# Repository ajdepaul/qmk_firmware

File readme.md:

# Custom 14x5 Keyboard QMK Fork

Forked from: https://github.com/qmk/qmk_firmware

I followed [this](https://github.com/ruiqimao/keyboard-pcb-guide) guide to design the PCB.

- KiCad PCB files can be found in the [pcb](pcb) directory.
- KiCad PCB files for a switch plate can found in the [plate](plate) directory.
- Laser cut case files can be found in the [case](case) directory.

Build with QMK CLI: `qmk compile -kb kb -km default`

Notes:
- I did not originally design the PCB with holes for screws. I ended up drilling
  holes in the PCB in safe locations for screws. The screw holes in the acrylic
  case cutouts line up with the holes that I drilled personally. If you want to
  rebuild the board, I recommend adding holes to the PCB and changing the hole
  placements in the acrylic case cutouts to match.
- I did not originally design the PCB with RGB LED strips in mind. The LED strip
  I am using is soldered directly onto some pins of the MCU. If you want RGB LED
  strip support, I recommend adding some soldering points to the PCB.
- I did not fill the PCB for the switch plate with copper, so it flexes a good
  amount. If you want to rebuild the board, I recommend modifying the PCB plate
  and filling it with copper to give a sturdier feel.

## Personal Keyboard Specs

- Switches: Lubed Cherry MX Clear with 62g springs
- Keycaps:
  - [KPrepublic Japanese Root base](https://kprepublic.com/collections/pbt-dye-sub-keycaps/products/kprepublic-139-japanese-root-japan-black-font-language-cherry-profile-dye-sub-keycap-pbt-for-gh60-xd60-xd84-cospad-tada68-87-104)
  - [Muted Copper Koi Fish artisan](https://www.etsy.com/shop/DreamKaps?ref=from_order_confirm_drawer_receipt_modal)
  - Cheap PBT black & gray blanks for modifiers

## Pictures

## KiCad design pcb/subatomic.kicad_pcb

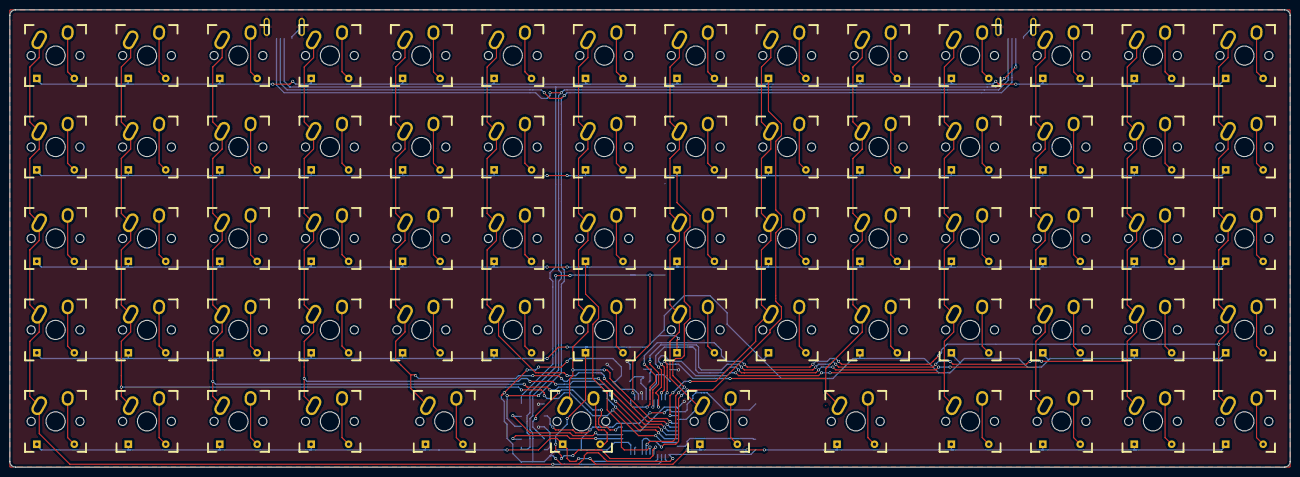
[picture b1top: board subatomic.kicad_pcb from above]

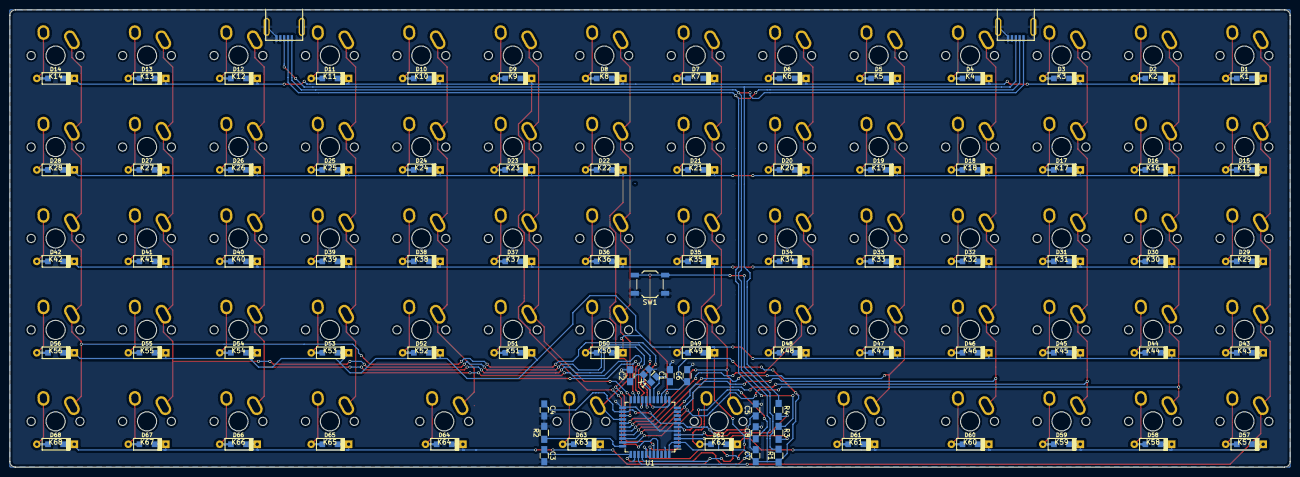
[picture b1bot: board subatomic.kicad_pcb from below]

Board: 2 copper layers, 266.7 x 95.3 mm, 153 parts (85 on the bottom side), 98 nets.

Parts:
C1, C2: 22p; C_0805_HandSoldering
C3, C4, C5, C6: 0.1u; C_0805_HandSoldering
C7: 4.7u; C_0805_HandSoldering
C8: 1u; C_0805_HandSoldering
D1, D2, D3, D4, D5, D6, D7, D8, D9, D10, D11, D12, D13, D14, D15, D16, D17, D18, D19, D20, D21, D22, D23, D24, D25, D26, D27, D28, D29, D30, D31, D32, D33, D34, D35, D36, D37, D38, D39, D40, D41, D42, D43, D44, D45, D46, D47, D48, D49, D50, D51, D52, D53, D54, D55, D56, D57, D58, D59, D60, D61, D62, D63, D64, D65, D66, D67, D68: D; D_SOD123_axial
J1, J2: USB_mini_micro_B; USB_miniB_hirose_5S8
K1, K2, K3, K4, K5, K6, K7, K8, K9, K10, K11, K12, K13, K14, K15, K16, K17, K18, K19, K20, K21, K22, K23, K24, K25, K26, K27, K28, K29, K30, K31, K32, K33, K34, K35, K36, K37, K38, K39, K40, K41, K42, K43, K44, K45, K46, K47, K48, K49, K50, K51, K52, K53, K54, K55, K56, K57, K58, K59, K60, K65, K66, K67, K68: KEYSW; Mx_Alps_100
K61, K62, K63, K64: KEYSW; Mx_Alps_150
R1, R2: 10k; R_0805_HandSoldering
R3, R4: 22; R_0805_HandSoldering
SW1: SW_PUSH; SW_SPST_TL3342
U1: ATMEGA32U4; TQFP-44_10x10mm_Pitch0.8mm
X1: XTAL_GND; crystal_FA238-TSX3225

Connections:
/col0: K1.1, K15.1, K29.1, K43.1, K57.1, U1.36
/col1: K2.1, K16.1, K30.1, K44.1, K58.1, U1.32
/col2: K3.1, K17.1, K31.1, K45.1, K59.1, U1.31
/col3: K4.1, K18.1, K32.1, K46.1, K60.1, U1.30
/col4: K5.1, K19.1, K33.1, K47.1, K61.1, U1.29
/col5: K6.1, K20.1, K34.1, K48.1, U1.28
/col6: K7.1, K21.1, K35.1, K49.1, K62.1, U1.27
/col7: K8.1, K22.1, K36.1, K50.1, K63.1, U1.26
/col8: K9.1, K23.1, K37.1, K51.1, U1.25
/col9: K10.1, K24.1, K38.1, K52.1, K64.1, U1.21
/col10: K11.1, K25.1, K39.1, K53.1, K65.1, U1.20
/col11: K12.1, K26.1, K40.1, K54.1, K66.1, U1.19
/col12: K13.1, K27.1, K41.1, K55.1, K67.1, U1.18
/col13: K14.1, K28.1, K42.1, K56.1, K68.1, U1.12
/row0: D1.1, D2.1, D3.1, D4.1, D5.1, D6.1, D7.1, D8.1, D9.1, D10.1, D11.1, D12.1, D13.1, D14.1, U1.41
/row1: D15.1, D16.1, D17.1, D18.1, D19.1, D20.1, D21.1, D22.1, D23.1, D24.1, D25.1, D26.1, D27.1, D28.1, U1.40
/row2: D29.1, D30.1, D31.1, D32.1, D33.1, D34.1, D35.1, D36.1, D37.1, D38.1, D39.1, D40.1, D41.1, D42.1, U1.39
/row3: D43.1, D44.1, D45.1, D46.1, D47.1, D48.1, D49.1, D50.1, D51.1, D52.1, D53.1, D54.1, D55.1, D56.1, U1.38
/row4: D57.1, D58.1, D59.1, D60.1, D61.1, D62.1, D63.1, D64.1, D65.1, D66.1, D67.1, D68.1, U1.37
GND: C1.2, C2.2, C3.2, C4.2, C5.2, C6.2, C7.2, C8.2, J1.5, J1.6, J2.5, J2.6, R2.2, SW1.1, U1.5, U1.15, U1.23, U1.35, U1.43, X1.3
unnamed: C1.1, U1.16, X1.1
unnamed: C2.1, U1.17, X1.2
unnamed: C8.1, U1.6
unnamed: D1.2, K1.2
unnamed: D2.2, K2.2
unnamed: D3.2, K3.2
unnamed: D4.2, K4.2
unnamed: D5.2, K5.2
unnamed: D6.2, K6.2
unnamed: D7.2, K7.2
unnamed: D8.2, K8.2
unnamed: D9.2, K9.2
unnamed: D10.2, K10.2
unnamed: D11.2, K11.2
unnamed: D12.2, K12.2
unnamed: D13.2, K13.2
unnamed: D14.2, K14.2
unnamed: D15.2, K15.2
unnamed: D16.2, K16.2
unnamed: D17.2, K17.2
unnamed: D18.2, K18.2
unnamed: D19.2, K19.2
unnamed: D20.2, K20.2
unnamed: D21.2, K21.2
unnamed: D22.2, K22.2
unnamed: D23.2, K23.2
unnamed: D24.2, K24.2
unnamed: D25.2, K25.2
unnamed: D26.2, K26.2
unnamed: D27.2, K27.2
unnamed: D28.2, K28.2
unnamed: D29.2, K29.2
unnamed: D30.2, K30.2
unnamed: D31.2, K31.2
unnamed: D32.2, K32.2
unnamed: D33.2, K33.2
unnamed: D34.2, K34.2
unnamed: D35.2, K35.2
unnamed: D36.2, K36.2
unnamed: D37.2, K37.2
unnamed: D38.2, K38.2
unnamed: D39.2, K39.2
unnamed: D40.2, K40.2
unnamed: D41.2, K41.2
unnamed: D42.2, K42.2
unnamed: D43.2, K43.2
unnamed: D44.2, K44.2
unnamed: D45.2, K45.2
unnamed: D46.2, K46.2
unnamed: D47.2, K47.2
unnamed: D48.2, K48.2
unnamed: D49.2, K49.2
unnamed: D50.2, K50.2
unnamed: D51.2, K51.2
unnamed: D52.2, K52.2
unnamed: D53.2, K53.2
unnamed: D54.2, K54.2
unnamed: D55.2, K55.2
unnamed: D56.2, K56.2
unnamed: D57.2, K57.2
unnamed: D58.2, K58.2
unnamed: D59.2, K59.2
unnamed: D60.2, K60.2
unnamed: D61.2, K61.2
unnamed: D62.2, K62.2
unnamed: D63.2, K63.2
unnamed: D64.2, K64.2
unnamed: D65.2, K65.2
unnamed: D66.2, K66.2
unnamed: D67.2, K67.2
unnamed: D68.2, K68.2
unnamed: J1.2, J2.2, R3.1
unnamed: J1.3, J2.3, R4.1
unnamed: R1.2, SW1.2, U1.13
unnamed: R2.1, U1.33
unnamed: R3.2, U1.3
unnamed: R4.2, U1.4
VCC: C3.1, C4.1, C5.1, C6.1, C7.1, J1.1, J2.1, R1.1, U1.2, U1.7, U1.14, U1.24, U1.34, U1.44

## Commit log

2021-09-15 Updated readme; added pcb, case, & plate
2021-09-17 Updated readme; added firmware
2021-09-17 Made red-orange slightly more orange
2021-09-17 added pictures
2021-09-17 added missing pictures
